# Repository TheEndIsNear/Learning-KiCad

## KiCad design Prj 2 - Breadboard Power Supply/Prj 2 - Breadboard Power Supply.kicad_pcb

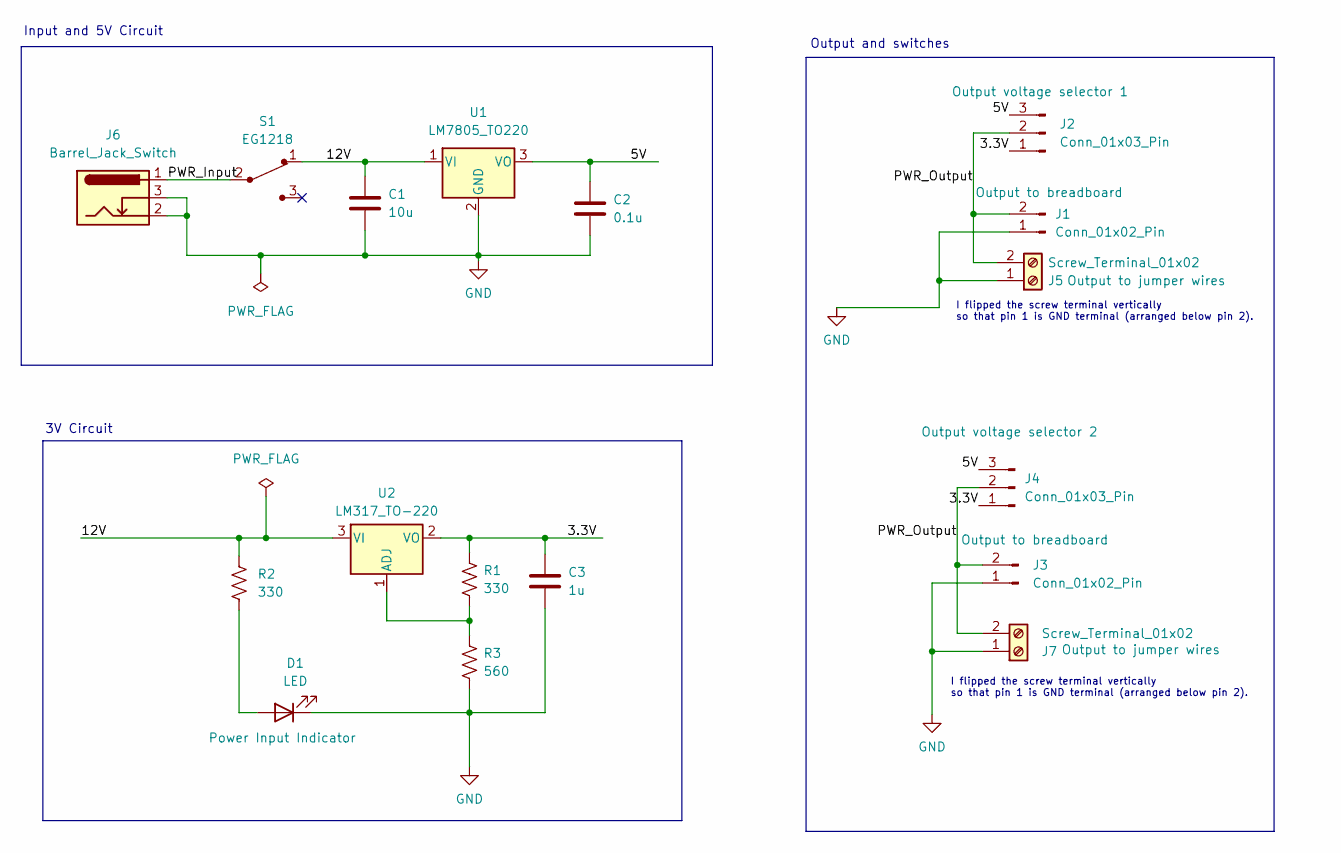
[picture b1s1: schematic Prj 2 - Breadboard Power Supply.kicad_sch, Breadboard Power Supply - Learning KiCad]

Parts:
C1: 10u; C_Disc_D5.0mm_W2.5mm_P2.50mm
C2: 0.1u; C_Disc_D5.0mm_W2.5mm_P2.50mm
C3: 1u; C_Disc_D5.0mm_W2.5mm_P2.50mm
D1: LED; LED_D5.0mm
J1, J3: Conn_01x02_Pin; PinHeader_1x02_P2.54mm_Vertical
J2, J4: Conn_01x03_Pin; PinHeader_1x03_P2.54mm_Vertical
J5, J7: Screw_Terminal_01x02; TerminalBlock_bornier-2_P5.08mm
J6: Barrel_Jack_Switch; BarrelJack_Horizontal
R1, R2: 330; R_Axial_DIN0204_L3.6mm_D1.6mm_P7.62mm_Horizontal
R3: 560; R_Axial_DIN0204_L3.6mm_D1.6mm_P7.62mm_Horizontal
S1: EG1218; Switch_Slide_11.6x4mm_EG1218; MPN EG1218; Digi-Key_PN EG1903-ND
U1: LM7805_TO220; TO-220-3_Vertical
U2: LM317_TO-220; TO-220-3_Vertical

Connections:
/3.3V: C3.1, J2.1, J4.1, R1.2, U2.2 (VO)
/5V: C2.1, J2.3, J4.3, U1.3 (VO)
/12V: C1.1, R2.2, S1.1, U1.1 (VI), U2.3 (VI)
/PWR_Input: J6.1, S1.2
/PWR_Output: J1.2, J2.2, J3.2, J4.2, J5.2, J7.2
GND: C1.2, C2.2, C3.2, D1.1 (K), J1.1, J3.1, J5.1, J6.2, J6.3, J7.1, R3.1, U1.2 (GND)
unnamed: D1.2 (A), R2.1
unnamed: R1.1, R3.2, U2.1 (ADJ)

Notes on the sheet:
I flipped the screw terminal vertically so that pin 1 is GND terminal (arranged below pin 2).
Output and switches
3V Circuit
Input and 5V Circuit

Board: 2 copper layers, 17 parts (0 on the bottom side), 8 nets, no tracks yet.

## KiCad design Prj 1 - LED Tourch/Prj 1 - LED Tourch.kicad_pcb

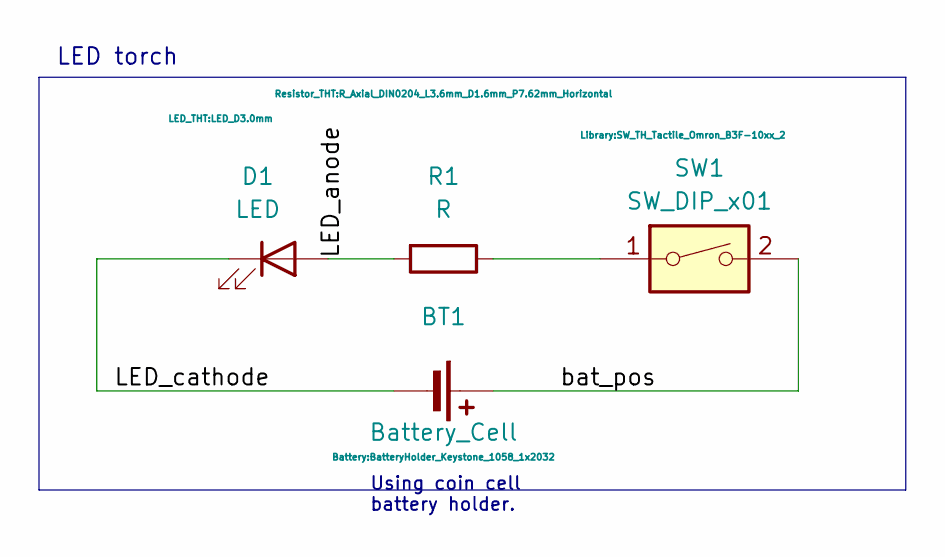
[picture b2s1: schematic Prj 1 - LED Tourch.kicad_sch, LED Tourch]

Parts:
BT1: Battery_Cell; BatteryHolder_Keystone_1058_1x2032
D1: LED; LED_D3.0mm
R1: R; R_Axial_DIN0204_L3.6mm_D1.6mm_P7.62mm_Horizontal
SW1: SW_DIP_x01; SW_TH_Tactile_Omron_B3F-10xx_2

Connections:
/LED_anode: D1.2 (A), R1.2
/LED_cathode: BT1.2 (-), D1.1 (K)
/bat_pos: BT1.1 (+), SW1.2
unnamed: R1.1, SW1.1

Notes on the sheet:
LED torch
Using coin cell battery holder.

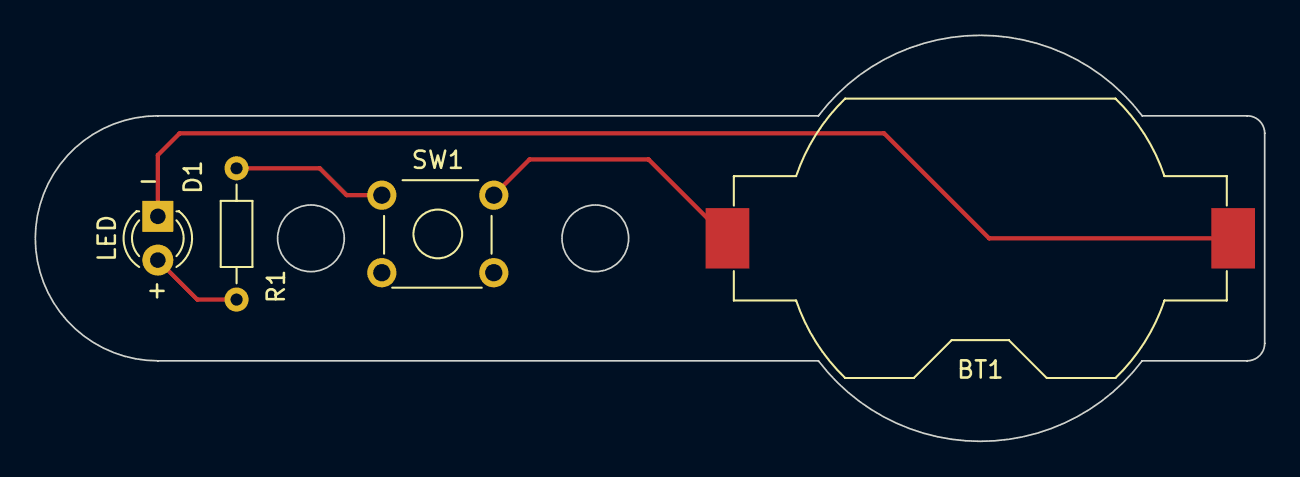
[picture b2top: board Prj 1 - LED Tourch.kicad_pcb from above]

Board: 2 copper layers, 71.4 x 23.6 mm, 4 parts (0 on the bottom side), 4 nets.

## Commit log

2024-01-29 add a first version of the led light
2024-01-30 update to include routing
2024-01-30 cut the edge for the battery
2024-01-30 round the back edges
2024-01-30 add graphics and silkscreen
2024-02-01 finalize the first version of the project
2024-02-01 start of a new project
2024-02-01 add the initial components
2024-02-01 add the components and move them into the areas where they will fit together
2024-02-01 associate all the components with pads
2024-02-01 final schematic for v1 of the power supply
2024-02-02 add the components to the pcb editor
2024-02-02 initial layout of the board
